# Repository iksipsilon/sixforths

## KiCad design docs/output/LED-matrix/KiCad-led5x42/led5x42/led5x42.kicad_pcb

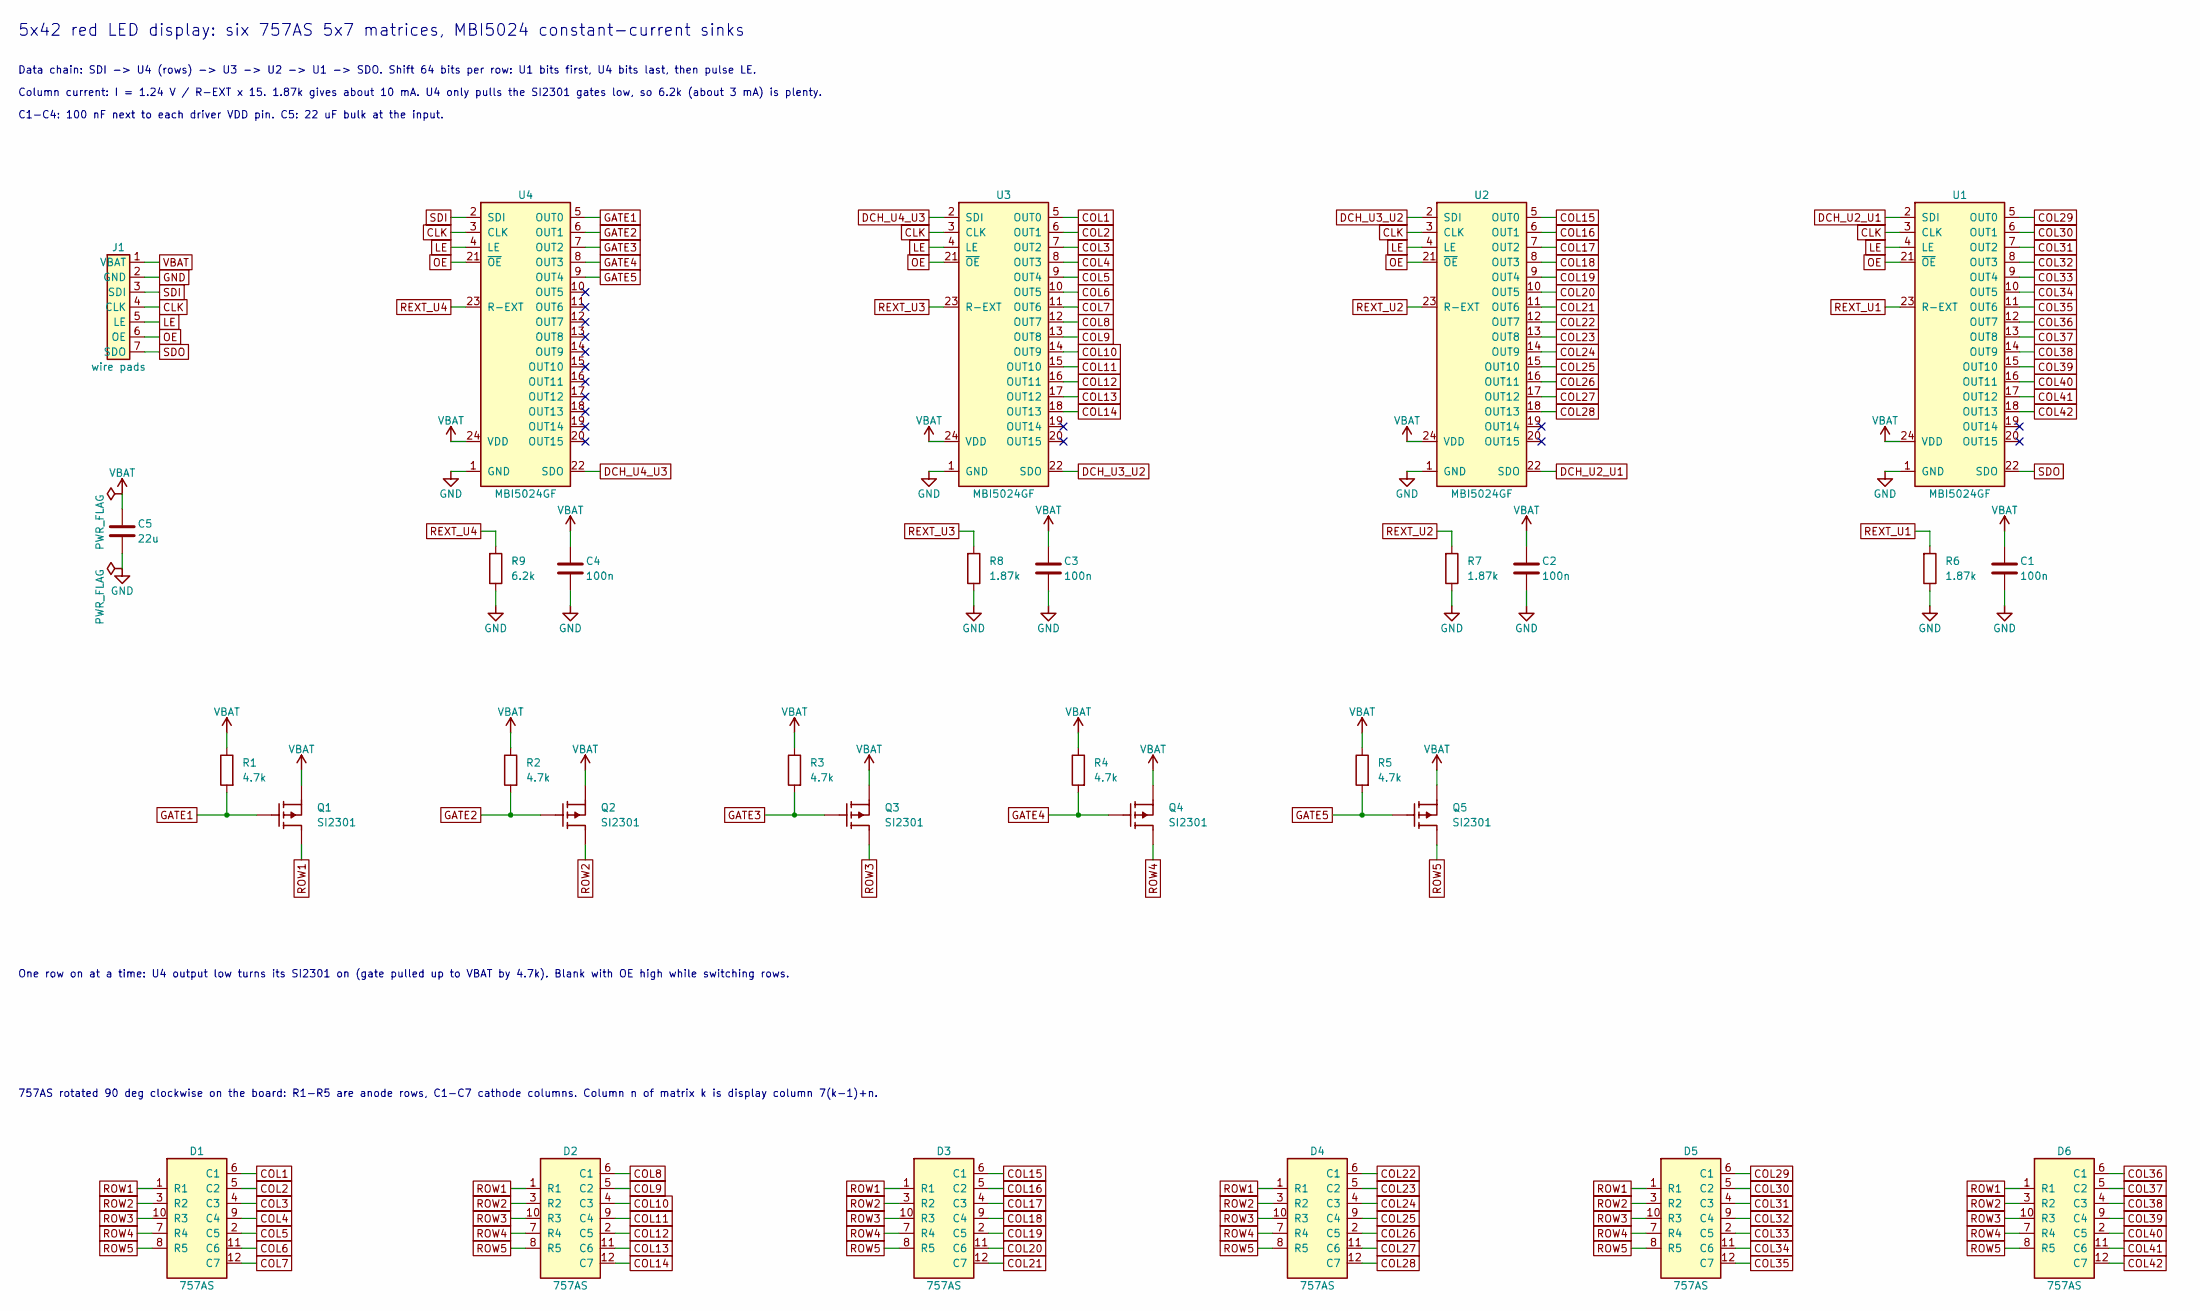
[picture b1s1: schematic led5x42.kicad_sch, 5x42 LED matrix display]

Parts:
C1, C2, C3, C4: 100n; C_0603
C5: 22u; C_0805
D1, D2, D3, D4, D5, D6: 757AS; 757AS_bent_castellated
J1: wire pads; WirePads_1x07_1.8mm
Q1, Q2, Q3, Q4, Q5: SI2301; SOT-23
R1, R2, R3, R4, R5: 4.7k; R_0603
R6, R7, R8: 1.87k; R_0603
R9: 6.2k; R_0603
U1, U2, U3, U4: MBI5024GF; SOP24_1.0mm_6.0x13.0mm

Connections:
CLK: J1.4 (CLK), U1.3 (CLK), U2.3 (CLK), U3.3 (CLK), U4.3 (CLK)
COL1: D1.6 (C1), U3.5 (OUT0)
COL2: D1.5 (C2), U3.6 (OUT1)
COL3: D1.4 (C3), U3.7 (OUT2)
COL4: D1.9 (C4), U3.8 (OUT3)
COL5: D1.2 (C5), U3.9 (OUT4)
COL6: D1.11 (C6), U3.10 (OUT5)
COL7: D1.12 (C7), U3.11 (OUT6)
COL8: D2.6 (C1), U3.12 (OUT7)
COL9: D2.5 (C2), U3.13 (OUT8)
COL10: D2.4 (C3), U3.14 (OUT9)
COL11: D2.9 (C4), U3.15 (OUT10)
COL12: D2.2 (C5), U3.16 (OUT11)
COL13: D2.11 (C6), U3.17 (OUT12)
COL14: D2.12 (C7), U3.18 (OUT13)
COL15: D3.6 (C1), U2.5 (OUT0)
COL16: D3.5 (C2), U2.6 (OUT1)
COL17: D3.4 (C3), U2.7 (OUT2)
COL18: D3.9 (C4), U2.8 (OUT3)
COL19: D3.2 (C5), U2.9 (OUT4)
COL20: D3.11 (C6), U2.10 (OUT5)
COL21: D3.12 (C7), U2.11 (OUT6)
COL22: D4.6 (C1), U2.12 (OUT7)
COL23: D4.5 (C2), U2.13 (OUT8)
COL24: D4.4 (C3), U2.14 (OUT9)
COL25: D4.9 (C4), U2.15 (OUT10)
COL26: D4.2 (C5), U2.16 (OUT11)
COL27: D4.11 (C6), U2.17 (OUT12)
COL28: D4.12 (C7), U2.18 (OUT13)
COL29: D5.6 (C1), U1.5 (OUT0)
COL30: D5.5 (C2), U1.6 (OUT1)
COL31: D5.4 (C3), U1.7 (OUT2)
COL32: D5.9 (C4), U1.8 (OUT3)
COL33: D5.2 (C5), U1.9 (OUT4)
COL34: D5.11 (C6), U1.10 (OUT5)
COL35: D5.12 (C7), U1.11 (OUT6)
COL36: D6.6 (C1), U1.12 (OUT7)
COL37: D6.5 (C2), U1.13 (OUT8)
COL38: D6.4 (C3), U1.14 (OUT9)
COL39: D6.9 (C4), U1.15 (OUT10)
COL40: D6.2 (C5), U1.16 (OUT11)
COL41: D6.11 (C6), U1.17 (OUT12)
COL42: D6.12 (C7), U1.18 (OUT13)
DCH_U2_U1: U1.2 (SDI), U2.22 (SDO)
DCH_U3_U2: U2.2 (SDI), U3.22 (SDO)
DCH_U4_U3: U3.2 (SDI), U4.22 (SDO)
GATE1: Q1.1 (G), R1.1, U4.5 (OUT0)
GATE2: Q2.1 (G), R2.1, U4.6 (OUT1)
GATE3: Q3.1 (G), R3.1, U4.7 (OUT2)
GATE4: Q4.1 (G), R4.1, U4.8 (OUT3)
GATE5: Q5.1 (G), R5.1, U4.9 (OUT4)
GND: C1.2, C2.2, C3.2, C4.2, C5.2, J1.2 (GND), R6.2, R7.2, R8.2, R9.2, U1.1 (GND), U2.1 (GND), U3.1 (GND), U4.1 (GND)
LE: J1.5 (LE), U1.4 (LE), U2.4 (LE), U3.4 (LE), U4.4 (LE)
OE: J1.6 (OE), U1.21 (~OE), U2.21 (~OE), U3.21 (~OE), U4.21 (~OE)
REXT_U1: R6.1, U1.23 (R-EXT)
REXT_U2: R7.1, U2.23 (R-EXT)
REXT_U3: R8.1, U3.23 (R-EXT)
REXT_U4: R9.1, U4.23 (R-EXT)
ROW1: D1.1 (R1), D2.1 (R1), D3.1 (R1), D4.1 (R1), D5.1 (R1), D6.1 (R1), Q1.3 (D)
ROW2: D1.3 (R2), D2.3 (R2), D3.3 (R2), D4.3 (R2), D5.3 (R2), D6.3 (R2), Q2.3 (D)
ROW3: D1.10 (R3), D2.10 (R3), D3.10 (R3), D4.10 (R3), D5.10 (R3), D6.10 (R3), Q3.3 (D)
ROW4: D1.7 (R4), D2.7 (R4), D3.7 (R4), D4.7 (R4), D5.7 (R4), D6.7 (R4), Q4.3 (D)
ROW5: D1.8 (R5), D2.8 (R5), D3.8 (R5), D4.8 (R5), D5.8 (R5), D6.8 (R5), Q5.3 (D)
SDI: J1.3 (SDI), U4.2 (SDI)
SDO: J1.7 (SDO), U1.22 (SDO)
VBAT: C1.1, C2.1, C3.1, C4.1, C5.1, J1.1 (VBAT), Q1.2 (S), Q2.2 (S), Q3.2 (S), Q4.2 (S), Q5.2 (S), R1.2, R2.2, R3.2, R4.2, R5.2, U1.24 (VDD), U2.24 (VDD), U3.24 (VDD), U4.24 (VDD)

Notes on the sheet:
5x42 red LED display: six 757AS 5x7 matrices, MBI5024 constant-current sinks
Data chain: SDI -> U4 (rows) -> U3 -> U2 -> U1 -> SDO. Shift 64 bits per row: U1 bits first, U4 bits last, then pulse LE.
Column current: I = 1.24 V / R-EXT x 15. 1.87k gives about 10 mA. U4 only pulls the SI2301 gates low, so 6.2k (about 3 mA) is plenty.
One row on at a time: U4 output low turns its SI2301 on (gate pulled up to VBAT by 4.7k). Blank with OE high while switching rows.
757AS rotated 90 deg clockwise on the board: R1-R5 are anode rows, C1-C7 cathode columns. Column n of matrix k is display column 7(k-1)+n.
C1-C4: 100 nF next to each driver VDD pin. C5: 22 uF bulk at the input.

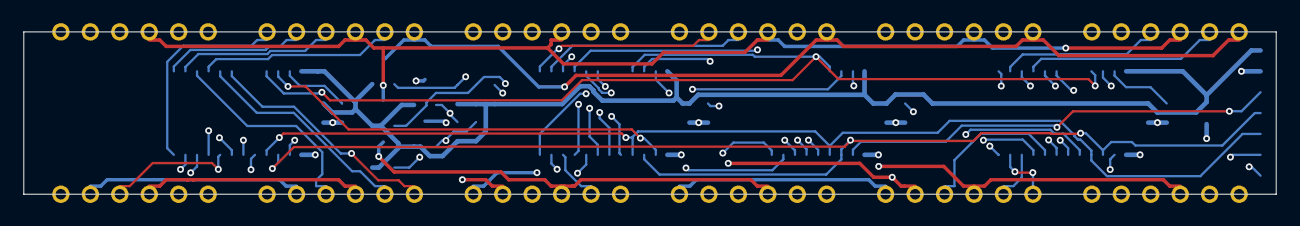
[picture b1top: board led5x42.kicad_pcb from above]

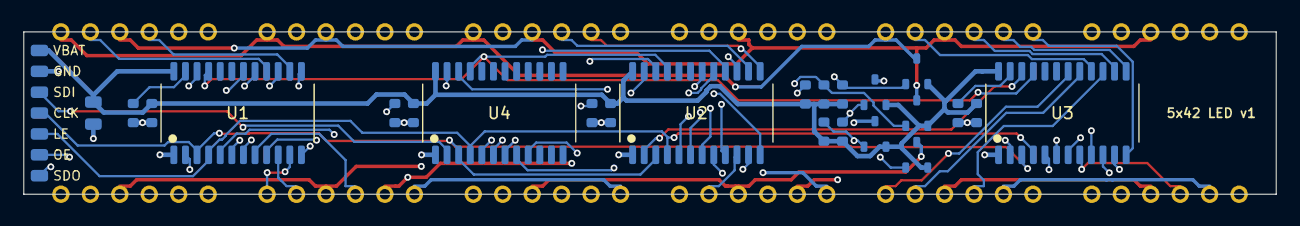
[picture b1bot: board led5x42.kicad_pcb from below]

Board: 4 copper layers, 108.0 x 14.0 mm, 30 parts (24 on the bottom side), 66 nets.
